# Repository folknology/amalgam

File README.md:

# Amalgam
Amalgam an OpenSource hardware fusion of FPGA and Cortex M7 Microcontroller in a [BlackEdge](https://github.com/folknology/BlackEdge) compatible layout, a project of the myStorm communtiy.

Current status is hardware design, you can see the developments we are making on my regular streams :
*  [Live Stream, 8pm BST](https://www.twitch.tv/folknology)
* [Historic streams](https://www.youtube.com/watch?v=79OoLG_Dxk0&list=PLXS9jyX9czzodpJNL-szsMfl0rOrZk4B7)
Or at the join us at the [myStorm community forum](https://forum.mystorm.uk)

We will be using an Alloy fusion framework on top of [nMigen](https://github.com/m-labs/nmigen) and [Circuit Python](https://github.com/adafruit/circuitpython) alonmg with verilog using [Yosys](https://github.com/YosysHQ/yosys)

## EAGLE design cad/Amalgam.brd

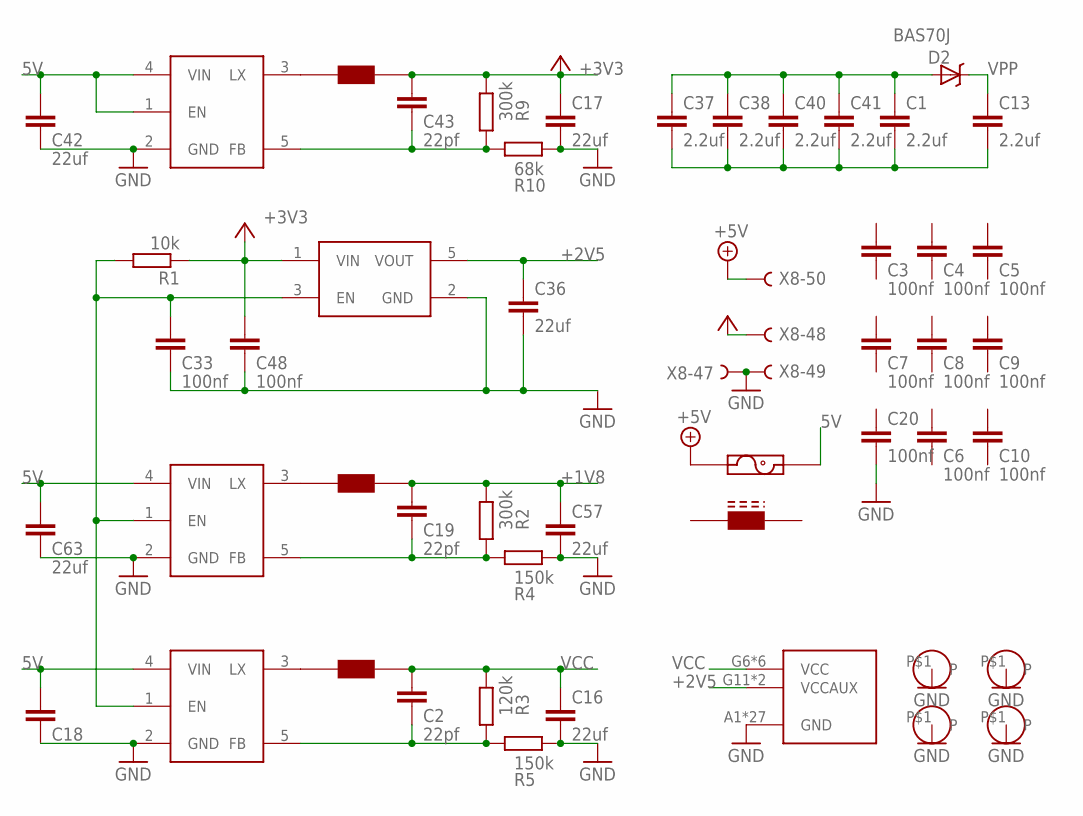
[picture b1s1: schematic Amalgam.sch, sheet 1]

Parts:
C1, C13, C37, C38, C40, C41: 2.2uf; C0603
C2, C19, C43: 22pf; C0402
C3, C4, C5, C6, C7, C8, C9, C10, C20, C33, C48: 100nf; C0402
C16, C17, C36, C57: 22uf; C0603
C18, C42, C63: 22uf; C0402
D2: BAS70J; SOD-323
IC7: NCP114; TSOP-5/SOT23-5
R1: 10k; R0402
R2, R9: 300k; R0402
R3: 120k; R0402
R4, R5: 150k; R0402
R10: 68k; R0402
U$1: PTC-1206; 1206
U$7, U$15, U$16, U$17: HOLE-2.5MM; 2.5MM-HOLE
U$12, U$13, U$20: AP3429/A; TSOP-5/SOT23-5
U$14: LFE5-XX256CABGA256; CABGA256
U$18, U$19, U$23: NRS4018; NRC4018
U$21: FERRITE_BEAD1206; 1206
X8: 1296-T50; 1296-50

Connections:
5V: C18.2, C42.2, C63.2, U$1.2, U$12.4 (VIN), U$13.4 (VIN), U$20.1 (EN), U$20.4 (VIN); also elsewhere on the board
+1V8: C19.2, C57.1, R2.2, U$19.P$2; also elsewhere on the board
+2V5: C36.1, IC7.5 (VOUT), U$14.G11 (VCCAUX), U$14.L7 (VCCAUX)
+3V3: C17.1, C43.2, C48.2, IC7.1 (VIN), R1.1, R9.2, U$23.P$2, X8.48; also elsewhere on the board
+5V: U$1.1, X8.50; also elsewhere on the board
GND: C16.2, C17.2, C18.1, C20.2, C33.1, C36.2, C42.1, C48.1, C57.2, C63.1, IC7.2 (GND), R4.2, R5.2, R10.2, U$7.P$1, U$12.2 (GND), U$13.2 (GND), U$14.A1 (GND), U$14.A16 (GND), U$14.D2 (GND), U$14.D15 (GND), U$14.F8 (GND), U$14.F9 (GND), U$14.G8 (GND), U$14.G10 (GND), U$14.H1 (GND), U$14.H8 (GND), U$14.H9 (GND), U$14.H10 (GND), U$14.H16 (GND), U$14.J8 (GND), U$14.J9 (GND), U$14.J10 (GND), U$14.K6 (GND), U$14.K7 (GND), U$14.K8 (GND), U$14.K9 (GND), U$14.K10 (GND), U$14.N2 (GND), U$14.N15 (GND), U$14.T1 (GND), U$14.T5 (GND), U$14.T12 (GND), U$14.T16 (GND), U$15.P$1, U$16.P$1, U$17.P$1, U$20.2 (GND), X8.47, X8.49; also elsewhere on the board
unnamed: C33.2, IC7.3 (EN), R1.2, U$12.1 (EN), U$13.1 (EN)
unnamed: C19.1, R2.1, R4.1, U$12.5 (FB)
unnamed: U$13.3 (LX), U$18.P$1
unnamed: U$12.3 (LX), U$19.P$1
unnamed: C2.1, R3.1, R5.1, U$13.5 (FB)
unnamed: C43.1, R9.1, R10.1, U$20.5 (FB)
unnamed: U$20.3 (LX), U$23.P$1
unnamed: C1.2, C13.2, C37.2, C38.2, C40.2, C41.2
unnamed: C1.1, C37.1, C38.1, C40.1, C41.1, D2.A
VCC: C2.2, C16.1, R3.2, U$14.G6 (VCC), U$14.G7 (VCC), U$14.G9 (VCC), U$14.L8 (VCC), U$14.L9 (VCC), U$14.L10 (VCC), U$18.P$2
VPP: C13.1, D2.C

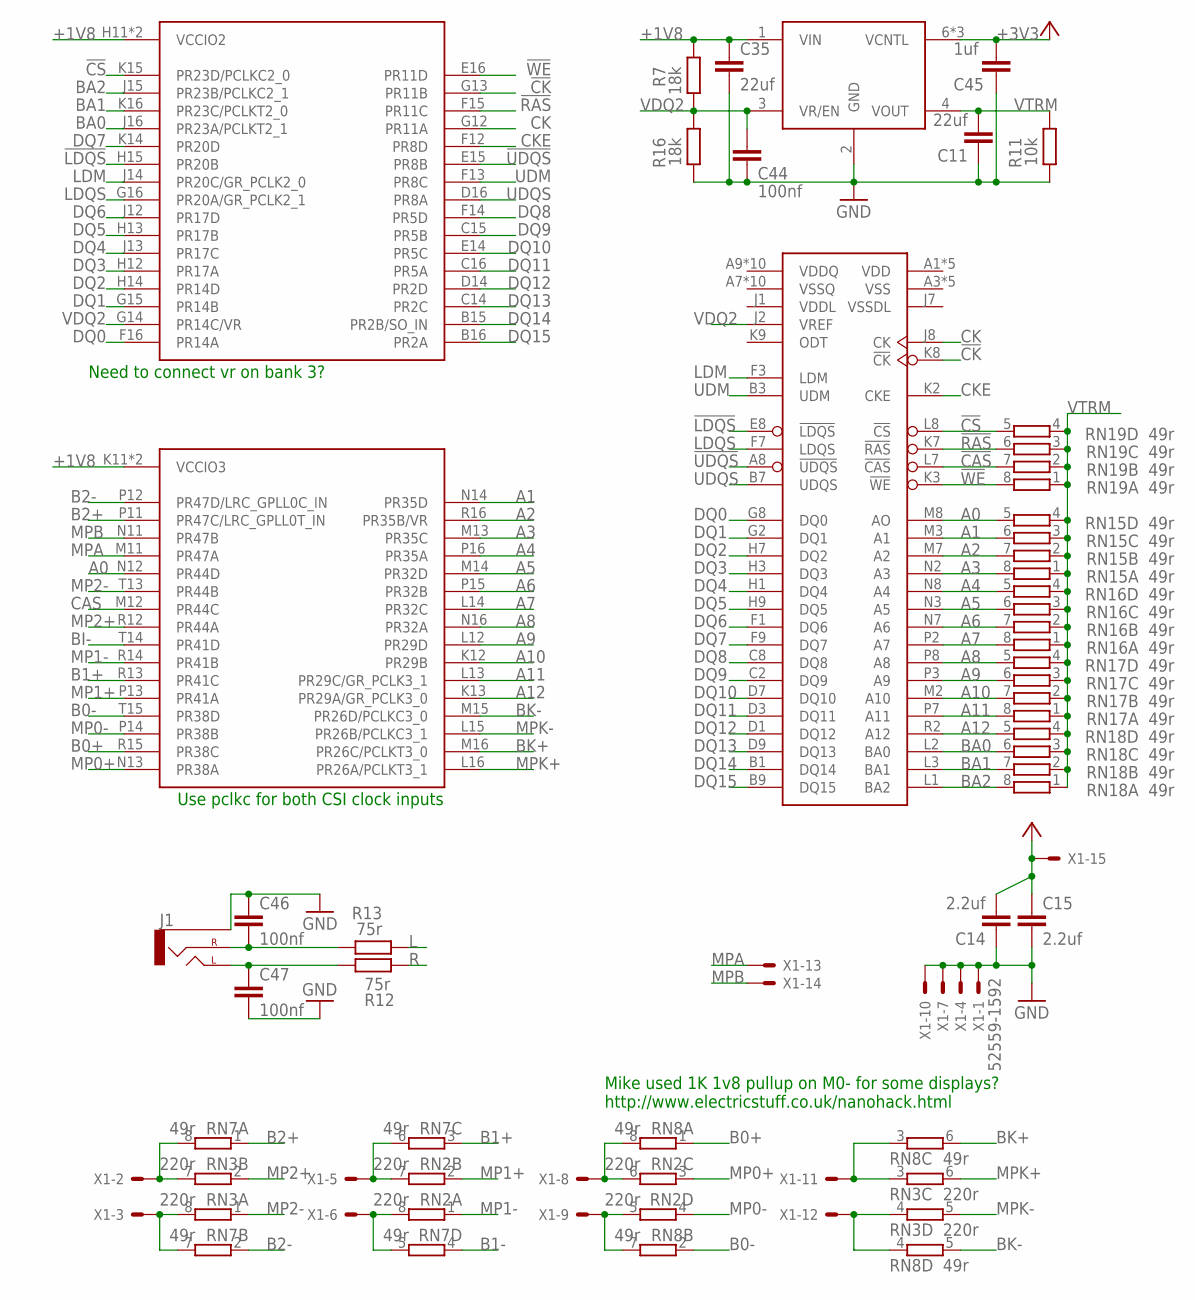
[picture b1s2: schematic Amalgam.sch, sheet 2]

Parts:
C11, C35: 22uf; C0603
C14, C15: 2.2uf; C0603
C44: 100nf; C0402
C45: 1uf; C0402
C46, C47: 100nf; C0603
J1: AUDIO_JACK_2.5MM_2.5MM_SMD; STEREOJACK2.5MM
R7, R16: 18k; R0402
R11: 10k; R0402
R12, R13: 75r; R0402
RN2, RN3: 220r; EXB38V
RN7, RN8, RN15, RN16, RN17, RN18, RN19: 49r; EXB38V
U$4: DDR2; WBGA-84
U$14: LFE5-XX256CABGA256; CABGA256
U$22: AP2303; SOIC-8-NARROW
X1: 52559-1592

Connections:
!CAS: RN19.7 (2), U$4.L7 (!CAS)
!CK: U$4.K8 (!CK), U$14.G13 (PR11B)
!CS: RN19.5 (2), U$4.L8 (!CS), U$14.K15 (PR23D/PCLKC2_0)
!LDQS: U$4.E8 (!LDQS), U$14.H15 (PR20B)
!RAS: RN19.6 (2), U$4.K7 (!RAS), U$14.F15 (PR11C)
!UDQS: U$4.A8 (!UDQS), U$14.E15 (PR8B)
!WE: RN19.8 (2), U$4.K3 (!WE), U$14.E16 (PR11D)
+1V8: C35.1, R7.1, U$14.H11 (VCCIO2), U$14.J11 (VCCIO2), U$14.K11 (VCCIO3), U$14.L11 (VCCIO3), U$22.1 (VIN); also elsewhere on the board
+3V3: C14.2, C15.1, C45.2, U$22.6 (VCNTL), U$22.7 (VCNTL), U$22.8 (VCNTL), X1.15; also elsewhere on the board
A0: RN15.5 (2), U$4.M8 (AO), U$14.N12 (PR44D)
A1: RN15.6 (2), U$4.M3 (A1), U$14.N14 (PR35D)
A2: RN15.7 (2), U$4.M7 (A2), U$14.R16 (PR35B/VR)
A3: RN15.8 (2), U$4.N2 (A3), U$14.M13 (PR35C)
A4: RN16.5 (2), U$4.N8 (A4), U$14.P16 (PR35A)
A5: RN16.6 (2), U$4.N3 (A5), U$14.M14 (PR32D)
A6: RN16.7 (2), U$4.N7 (A6), U$14.P15 (PR32B)
A7: RN16.8 (2), U$4.P2 (A7), U$14.L14 (PR32C)
A8: RN17.5 (2), U$4.P8 (A8), U$14.N16 (PR32A)
A9: RN17.6 (2), U$4.P3 (A9), U$14.L12 (PR29D)
A10: RN17.7 (2), U$4.M2 (A10), U$14.K12 (PR29B)
A11: RN17.8 (2), U$4.P7 (A11), U$14.L13 (PR29C/GR_PCLK3_1)
A12: RN18.5 (2), U$4.R2 (A12), U$14.K13 (PR29A/GR_PCLK3_0)
B0+: RN8.1, U$14.R15 (PR38C)
B0-: RN8.2 (1), U$14.T15 (PR38D)
B1+: RN7.3 (1), U$14.R13 (PR41C)
B1-: RN7.4 (1)
B2+: RN7.1, U$14.P11 (PR47C/LRC_GPLL0T_IN)
B2-: RN7.2 (1), U$14.P12 (PR47D/LRC_GPLL0C_IN)
BA0: RN18.6 (2), U$4.L2 (BA0), U$14.J16 (PR23A/PCLKT2_1)
BA1: RN18.7 (2), U$4.L3 (BA1), U$14.K16 (PR23C/PCLKT2_0)
BA2: RN18.8 (2), U$4.L1 (BA2), U$14.J15 (PR23B/PCLKC2_1)
BI-: U$14.T14 (PR41D)
BK+: RN8.6 (2), U$14.M16 (PR26C/PCLKT3_0)
BK-: RN8.5 (2), U$14.M15 (PR26D/PCLKC3_0)
CAS: U$14.M12 (PR44C)
CK: U$4.J8 (CK), U$14.G12 (PR11A)
CKE: U$4.K2 (CKE), U$14.F12 (PR8D)
DQ0: U$4.G8 (DQ0), U$14.F16 (PR14A)
DQ1: U$4.G2 (DQ1), U$14.G15 (PR14B)
DQ2: U$4.H7 (DQ2), U$14.H14 (PR14D)
DQ3: U$4.H3 (DQ3), U$14.H12 (PR17A)
DQ4: U$4.H1 (DQ4), U$14.J13 (PR17C)
DQ5: U$4.H9 (DQ5), U$14.H13 (PR17B)
DQ6: U$4.F1 (DQ6), U$14.J12 (PR17D)
DQ7: U$4.F9 (DQ7), U$14.K14 (PR20D)
DQ8: U$4.C8 (DQ8), U$14.F14 (PR5D)
DQ9: U$4.C2 (DQ9), U$14.C15 (PR5B)
DQ10: U$4.D7 (DQ10), U$14.E14 (PR5C)
DQ11: U$4.D3 (DQ11), U$14.C16 (PR5A)
DQ12: U$4.D1 (DQ12), U$14.D14 (PR2D)
DQ13: U$4.D9 (DQ13), U$14.C14 (PR2C)
DQ14: U$4.B1 (DQ14), U$14.B15 (PR2B/SO_IN)
DQ15: U$4.B9 (DQ15), U$14.B16 (PR2A)
GND: C11.1, C14.1, C15.2, C35.2, C44.1, C45.1, C46.1, C47.2, J1.5 (SLEEVE), R11.2, R16.2, U$22.2 (GND), X1.1, X1.4, X1.7, X1.10; also elsewhere on the board
L: R13.1; also elsewhere on the board
LDM: U$4.F3 (LDM), U$14.J14 (PR20C/GR_PCLK2_0)
LDQS: U$4.F7 (LDQS), U$14.G16 (PR20A/GR_PCLK2_1)
MP0+: RN2.3 (1), U$14.N13 (PR38A)
MP0-: RN2.4 (1), U$14.P14 (PR38B)
MP1+: RN2.2 (1), U$14.P13 (PR41A)
MP1-: RN2.1, U$14.R14 (PR41B)
MP2+: RN3.2 (1), U$14.R12 (PR44A)
MP2-: RN3.1, U$14.T13 (PR44B)
MPA: U$14.M11 (PR47A), X1.13
MPB: U$14.N11 (PR47B), X1.14
MPK+: RN3.6 (2), U$14.L16 (PR26A/PCLKT3_1)
MPK-: RN3.5 (2), U$14.L15 (PR26B/PCLKC3_1)
unnamed: RN3.3 (1), RN8.3 (1), X1.11
unnamed: RN3.4 (1), RN8.4 (1), X1.12
unnamed: RN2.6 (2), RN8.8 (2), X1.8
unnamed: RN2.5 (2), RN8.7 (2), X1.9
unnamed: RN2.7 (2), RN7.6 (2), X1.5
unnamed: RN2.8 (2), RN7.5 (2), X1.6
unnamed: RN3.8 (2), RN7.7 (2), X1.3
unnamed: RN3.7 (2), RN7.8 (2), X1.2
unnamed: C46.2, J1.4 (RIGHT), R13.2
unnamed: C47.1, J1.1 (LEFT), R12.1
R: R12.2; also elsewhere on the board
UDM: U$4.B3 (UDM), U$14.F13 (PR8C)
UDQS: U$4.B7 (UDQS), U$14.D16 (PR8A)
VDQ2: C44.2, R7.2, R16.1, U$4.J2 (VREF), U$14.G14 (PR14C/VR), U$22.3 (VR/EN)
VTRM: C11.2, R11.1, RN15.1, RN15.2 (1), RN15.3 (1), RN15.4 (1), RN16.1, RN16.2 (1), RN16.3 (1), RN16.4 (1), RN17.1, RN17.2 (1), RN17.3 (1), RN17.4 (1), RN18.1, RN18.2 (1), RN18.3 (1), RN18.4 (1), RN19.1, RN19.2 (1), RN19.3 (1), RN19.4 (1), U$22.4 (VOUT)

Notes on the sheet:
Need to connect vr on bank 3?
Use pclkc for both CSI clock inputs
Mike used 1K 1v8 pullup on M0- for some displays? http://www.electricstuff.co.uk/nanohack.html

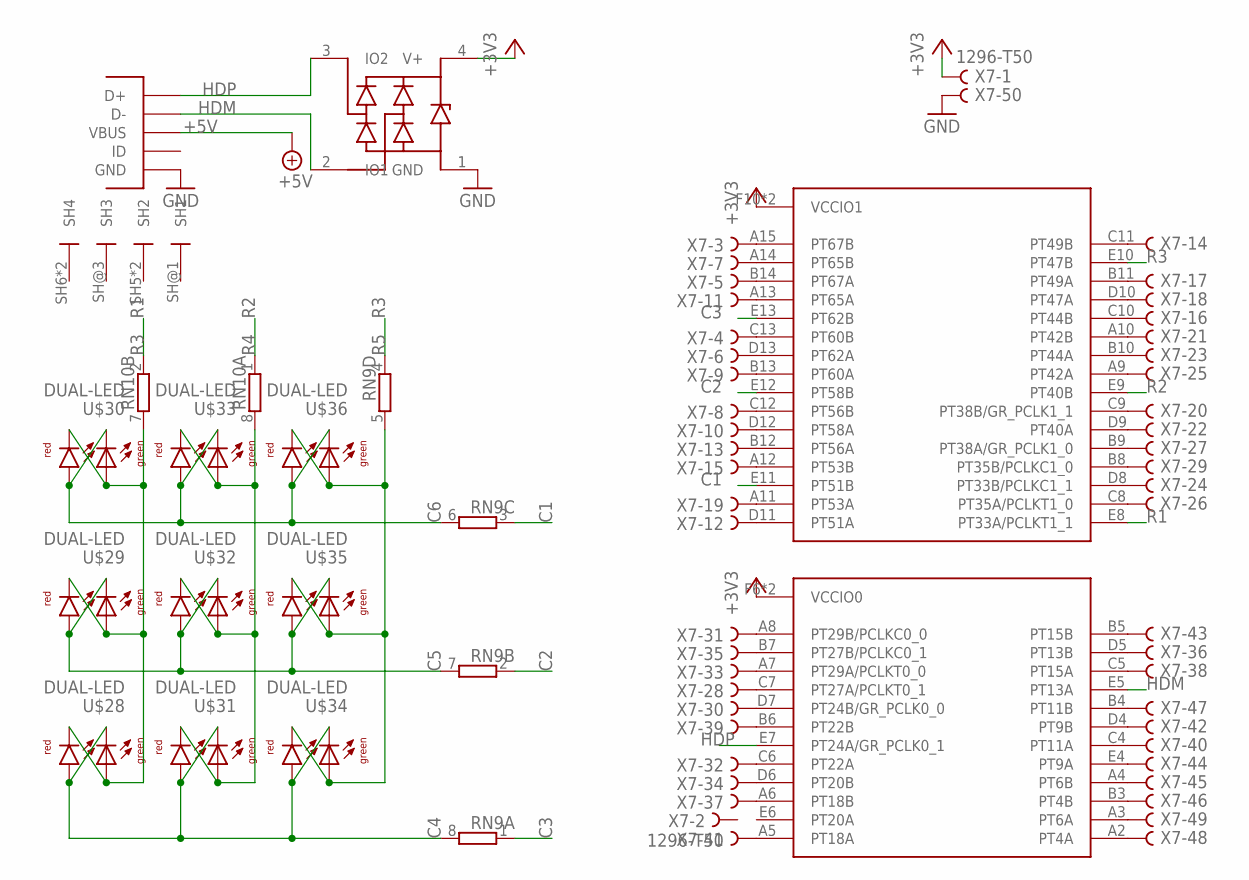
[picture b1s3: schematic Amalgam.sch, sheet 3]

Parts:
ESD1: PRTR5V0U2X; SOT143B
RN9, RN10: 4R-NEXB38V; EXB38V
U$11: FCI-MICROUSB-B-PEG; MICROUSB-B-PEG
U$14: LFE5-XX256CABGA256; CABGA256
U$28, U$29, U$30, U$31, U$32, U$33, U$34, U$35, U$36: DUAL-LED; DUAL-0603
X7: 1296-T50; 1296-50

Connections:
+3V3: ESD1.4 (V+), U$14.F6 (VCCIO0), U$14.F7 (VCCIO0), U$14.F10 (VCCIO1), U$14.F11 (VCCIO1), X7.1; also elsewhere on the board
+5V: U$11.P$1 (VBUS); also elsewhere on the board
C1: RN9.3 (1), U$14.E11 (PT51B)
C2: RN9.2 (1), U$14.E12 (PT58B)
C3: RN9.1, U$14.E13 (PT62B)
C4: RN9.8 (2), U$28.A1 (AR), U$28.C2 (CG), U$31.A1 (AR), U$31.C2 (CG), U$34.A1 (AR), U$34.C2 (CG)
C5: RN9.7 (2), U$29.A1 (AR), U$29.C2 (CG), U$32.A1 (AR), U$32.C2 (CG), U$35.A1 (AR), U$35.C2 (CG)
C6: RN9.6 (2), U$30.A1 (AR), U$30.C2 (CG), U$33.A1 (AR), U$33.C2 (CG), U$36.A1 (AR), U$36.C2 (CG)
GND: ESD1.1 (GND), U$11.P$5 (GND), X7.50; also elsewhere on the board
HDM: ESD1.2 (IO1), U$11.P$2 (D-), U$14.E5 (PT13A)
HDP: ESD1.3 (IO2), U$11.P$3 (D+), U$14.E7 (PT24A/GR_PCLK0_1)
unnamed: U$14.B3 (PT4B), X7.46
unnamed: U$14.A2 (PT4A), X7.48
unnamed: U$14.A15 (PT67B), X7.3
unnamed: U$14.B14 (PT67A), X7.5
unnamed: U$14.A14 (PT65B), X7.7
unnamed: U$14.B13 (PT60A), X7.9
unnamed: U$14.A13 (PT65A), X7.11
unnamed: U$14.B12 (PT56A), X7.13
unnamed: U$14.A12 (PT53B), X7.15
unnamed: U$14.B11 (PT49A), X7.17
unnamed: U$14.A11 (PT53A), X7.19
unnamed: U$14.C13 (PT60B), X7.4
unnamed: U$14.D13 (PT62A), X7.6
unnamed: U$14.C12 (PT56B), X7.8
unnamed: U$14.D12 (PT58A), X7.10
unnamed: U$14.A8 (PT29B/PCLKC0_0), X7.31
unnamed: U$14.A7 (PT29A/PCLKT0_0), X7.33
unnamed: U$14.B7 (PT27B/PCLKC0_1), X7.35
unnamed: U$14.A6 (PT18B), X7.37
unnamed: U$14.B6 (PT22B), X7.39
unnamed: U$14.A5 (PT18A), X7.41
unnamed: U$14.B5 (PT15B), X7.43
unnamed: U$14.C7 (PT27A/PCLKT0_1), X7.28
unnamed: U$14.D7 (PT24B/GR_PCLK0_0), X7.30
unnamed: U$14.C6 (PT22A), X7.32
unnamed: U$14.D6 (PT20B), X7.34
unnamed: U$14.D5 (PT13B), X7.36
unnamed: U$14.B4 (PT11B), X7.47
unnamed: U$14.A4 (PT6B), X7.45
unnamed: U$14.A3 (PT6A), X7.49
unnamed: U$14.D11 (PT51A), X7.12
unnamed: U$14.C11 (PT49B), X7.14
unnamed: U$14.C10 (PT44B), X7.16
unnamed: U$14.D10 (PT47A), X7.18
unnamed: U$14.A10 (PT42B), X7.21
unnamed: U$14.B10 (PT44A), X7.23
unnamed: U$14.A9 (PT42A), X7.25
unnamed: U$14.B9 (PT38A/GR_PCLK1_0), X7.27
unnamed: U$14.B8 (PT35B/PCLKC1_0), X7.29
unnamed: U$14.C9 (PT38B/GR_PCLK1_1), X7.20
unnamed: U$14.D9 (PT40A), X7.22
unnamed: U$14.D8 (PT33B/PCLKC1_1), X7.24
unnamed: U$14.C8 (PT35A/PCLKT1_0), X7.26
unnamed: U$14.C5 (PT15A), X7.38
unnamed: U$14.C4 (PT11A), X7.40
unnamed: U$14.D4 (PT9B), X7.42
unnamed: U$14.E4 (PT9A), X7.44
R1: RN10.2 (1), U$14.E8 (PT33A/PCLKT1_1)
R2: RN10.1, U$14.E9 (PT40B)
R3: RN9.4 (1), RN10.7 (2), U$14.E10 (PT47B), U$28.A2 (AG), U$28.C1 (CR), U$29.A2 (AG), U$29.C1 (CR), U$30.A2 (AG), U$30.C1 (CR)
R4: RN10.8 (2), U$31.A2 (AG), U$31.C1 (CR), U$32.A2 (AG), U$32.C1 (CR), U$33.A2 (AG), U$33.C1 (CR)
R5: RN9.5 (2), U$34.A2 (AG), U$34.C1 (CR), U$35.A2 (AG), U$35.C1 (CR), U$36.A2 (AG), U$36.C1 (CR)

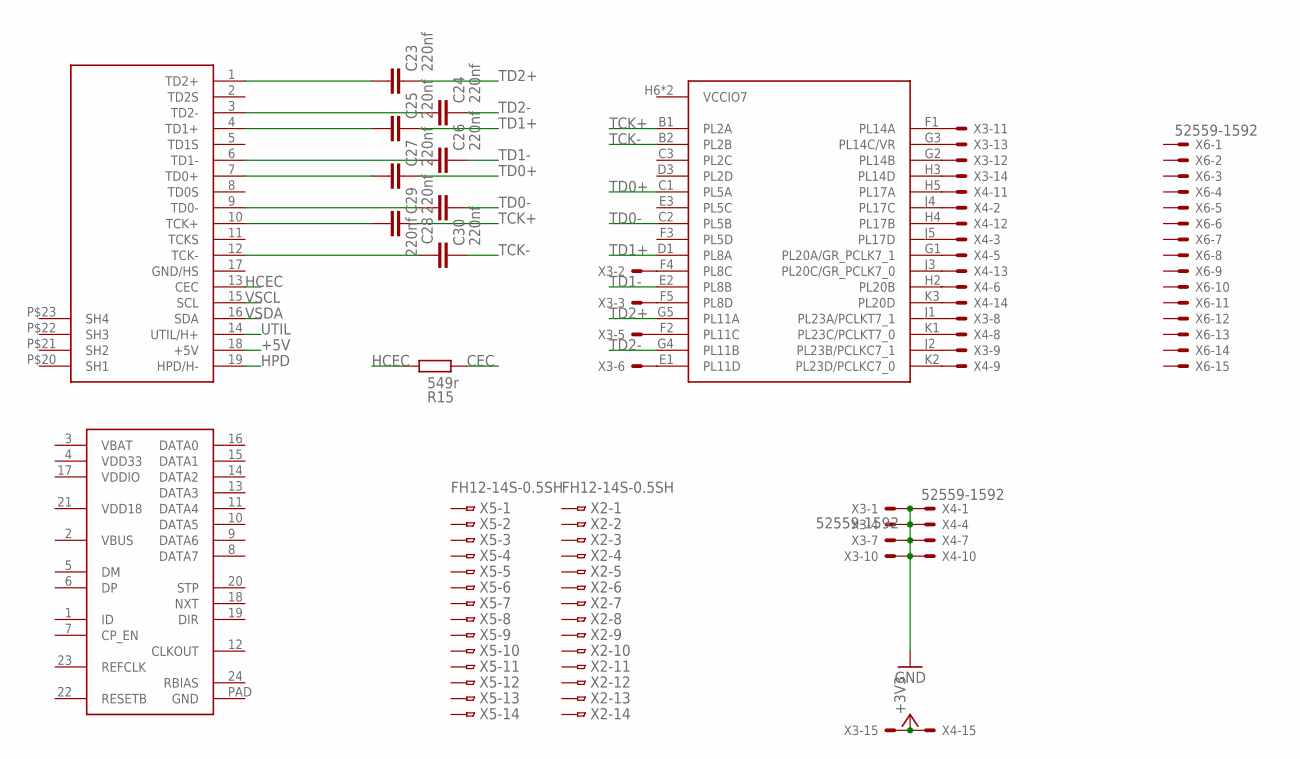
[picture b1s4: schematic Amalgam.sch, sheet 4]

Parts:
C23, C24, C25, C26, C27, C28, C29, C30: 220nf; C0402
R15: 549r; R0402
U$9: HD10-001_HDMIMINI-HDMI; MINI-HDMI
U$14: LFE5-XX256CABGA256; CABGA256
U$25: USB3318-QFN24; 24-QFN
X2, X5: FH12-14S-0.5SH
X3, X4, X6: 52559-1592

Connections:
+3V3: X3.15, X4.15; also elsewhere on the board
+5V: U$9.18 (+5V); also elsewhere on the board
CEC: R15.2; also elsewhere on the board
GND: U$25.PAD (GND), X3.1, X3.4, X3.7, X3.10, X4.1, X4.4, X4.7, X4.10; also elsewhere on the board
HCEC: R15.1, U$9.13 (CEC)
HPD: U$9.19 (HPD/H-); also elsewhere on the board
unnamed: U$14.K3 (PL20D), X4.14
unnamed: U$14.J3 (PL20C/GR_PCLK7_0), X4.13
unnamed: U$14.J1 (PL23A/PCLKT7_1), X3.8
unnamed: U$14.J2 (PL23B/PCLKC7_1), X3.9
unnamed: U$14.K1 (PL23C/PCLKT7_0), X4.8
unnamed: U$14.K2 (PL23D/PCLKC7_0), X4.9
unnamed: U$14.H2 (PL20B), X4.6
unnamed: U$14.G1 (PL20A/GR_PCLK7_1), X4.5
unnamed: U$14.J5 (PL17D), X4.3
unnamed: U$14.J4 (PL17C), X4.2
unnamed: U$14.H4 (PL17B), X4.12
unnamed: U$14.H5 (PL17A), X4.11
unnamed: U$14.H3 (PL14D), X3.14
unnamed: U$14.G3 (PL14C/VR), X3.13
unnamed: U$14.G2 (PL14B), X3.12
unnamed: U$14.F1 (PL14A), X3.11
unnamed: U$14.E1 (PL11D), X3.6
unnamed: U$14.F2 (PL11C), X3.5
unnamed: U$14.F5 (PL8D), X3.3
unnamed: C23.2, U$9.1 (TD2+)
unnamed: C24.2, U$9.3 (TD2-)
unnamed: C25.2, U$9.4 (TD1+)
unnamed: C26.2, U$9.6 (TD1-)
unnamed: C27.2, U$9.7 (TD0+)
unnamed: C28.1, U$9.9 (TD0-)
unnamed: C29.2, U$9.10 (TCK+)
unnamed: U$14.F4 (PL8C), X3.2
unnamed: C30.2, U$9.12 (TCK-)
TCK+: C29.1, U$14.B1 (PL2A)
TCK-: C30.1, U$14.B2 (PL2B)
TD0+: C27.1, U$14.C1 (PL5A)
TD0-: C28.2, U$14.C2 (PL5B)
TD1+: C25.1, U$14.D1 (PL8A)
TD1-: C26.1, U$14.E2 (PL8B)
TD2+: C23.1, U$14.G5 (PL11A)
TD2-: C24.1, U$14.G4 (PL11B)
UTIL: U$9.14 (UTIL/H+)
VBAT: U$25.3 (VBAT)
VDD18: U$25.21 (VDD18)
VDD33: U$25.4 (VDD33)
VDDIO: U$25.17 (VDDIO)
VSCL: U$9.15 (SCL); also elsewhere on the board
VSDA: U$9.16 (SDA); also elsewhere on the board

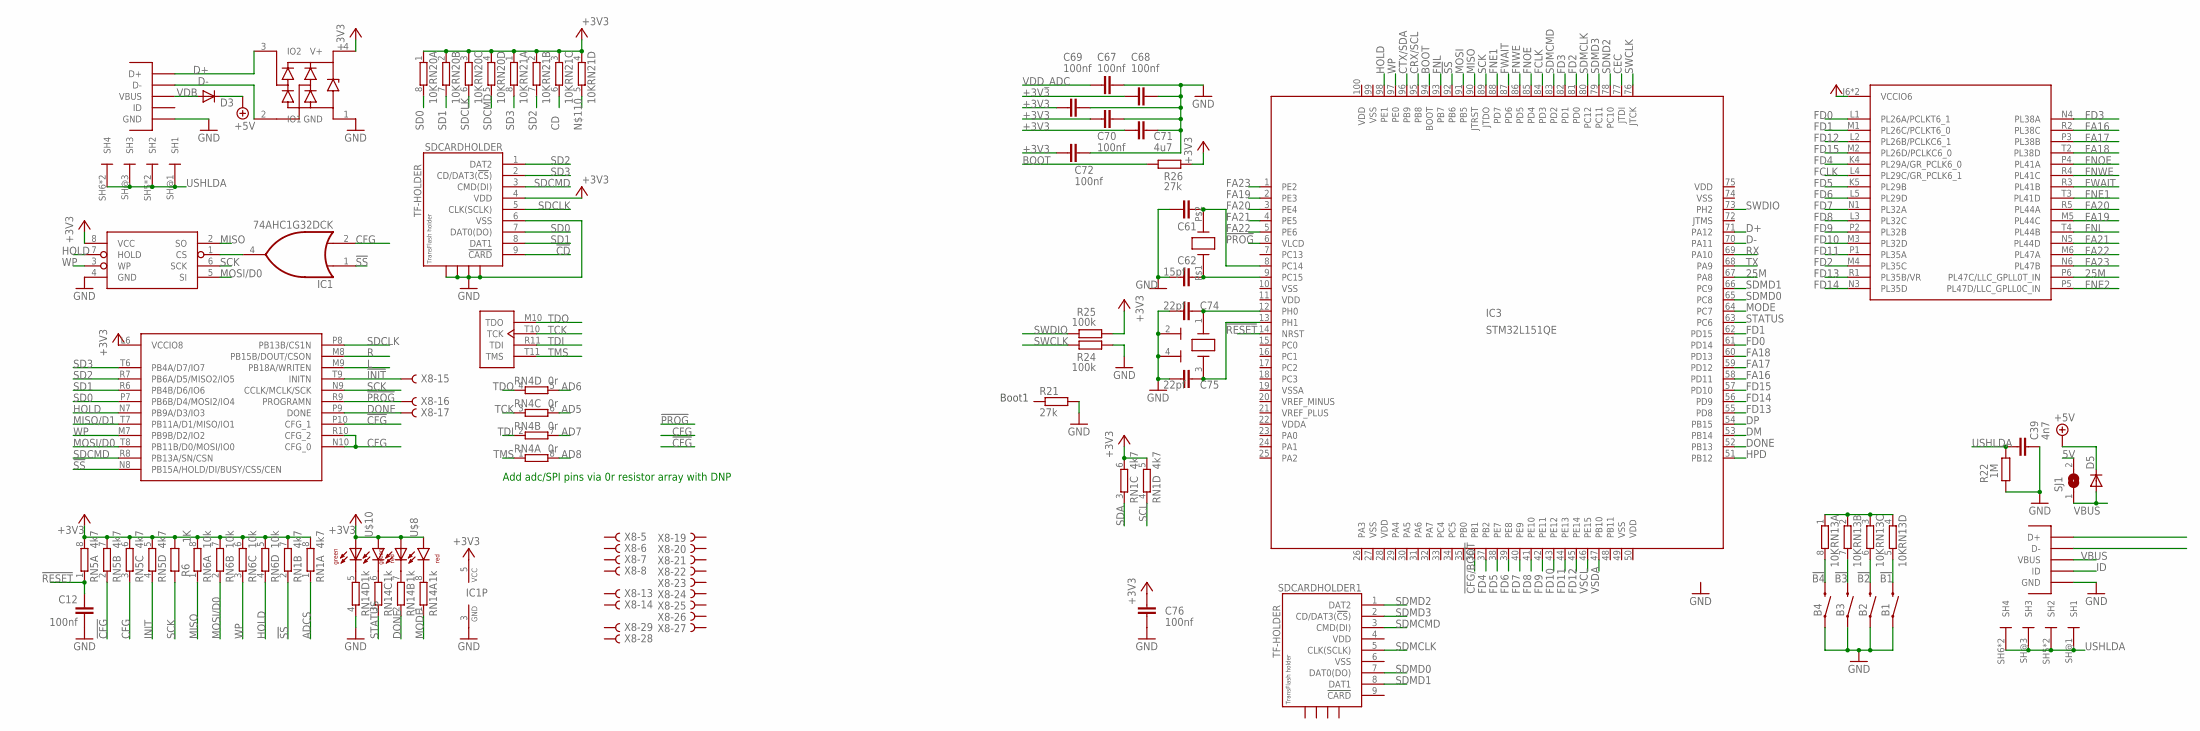
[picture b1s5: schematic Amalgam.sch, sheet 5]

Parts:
B1, B2, B3, B4: RS SWITCH; TACTILE-SWITCH-1101NE
C12, C67, C68, C69, C70, C72, C76: 100nf; C0402
C39: 4n7; C0402
C61, C62: 15pf; C0402
C71: 4u7; C0402
C74, C75: 22pf; C0402
D3, D5: DIODE-SOD123; SOD123
ESD2: PRTR5V0U2X; SOT143B
IC1: 74AHC1G32DCK; SC70-5
IC3: STM32L151QE; LQFP100_14X14
R6: 1K; R0402
R21, R26: 27k; R0402
R22: 1M; R0402
R24, R25: 100k; R0402
RN1, RN5: 4k7; EXB38V
RN4: 0r; EXB38V
RN6: 10k; EXB38V
RN13, RN20, RN21: 10K; EXB38V
RN14: 1k; EXB38V
SDCARDHOLDER, SDCARDHOLDER1: TF-HOLDER; TF-PULL
SJ1: SJ
U$2: AT25SDF041A; SOIC-8-NARROW
U$3: FC-135; FC135
U$5, U$6: FCI-MICROUSB-B-PEG; MICROUSB-B-PEG
U$8, U$10: DUAL-LED; DUAL-0603
U$14: LFE5-XX256CABGA256; CABGA256
X8: 1296-T50; 1296-50
Y3: 12MZ; CRYSTAL-3.2X2.5

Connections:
5V: SJ1.2; also elsewhere on the board
25M: IC3.67 (PA8), U$14.P6 (PL47C/LLC_GPLL0T_IN)
!B1: B1.2, RN13.5 (2)
!B2: B2.2, RN13.6 (2)
!B3: B3.2, RN13.7 (2)
!B4: B4.2, RN13.8 (2)
!CD: SDCARDHOLDER.9 (!CARD)
!CFG: RN5.2 (1), U$14.P10 (CFG_1)
!CFG/BOOT: IC3.36 (PB1)
!INIT: U$14.T9 (INITN), X8.15
!PROG: IC3.6 (VLCD), U$14.R9 (PROGRAMN), X8.16
!RESET: C12.1, IC3.14 (NRST), RN5.1
!SS: IC1.1 (I0), IC3.92 (PB6), RN1.2 (1), U$14.N8 (PB15A/HOLD/DI/BUSY/CSS/CEN)
+3V3: C68.2, C69.2, C70.2, C71.2, C72.2, C76.1, ESD2.4 (V+), IC1.5 (VCC), R6.2, R25.1, R26.2, RN1.5 (2), RN1.6 (2), RN1.7 (2), RN1.8 (2), RN5.5 (2), RN5.6 (2), RN5.7 (2), RN5.8 (2), RN6.5 (2), RN6.6 (2), RN6.7 (2), RN6.8 (2), RN20.1, RN20.2 (1), RN20.3 (1), RN20.4 (1), RN21.1, RN21.2 (1), RN21.3 (1), RN21.4 (1), SDCARDHOLDER.4 (VDD), U$2.8 (VCC), U$8.A1 (AR), U$8.A2 (AG), U$10.A1 (AR), U$10.A2 (AG), U$14.J6 (VCCIO6), U$14.J7 (VCCIO6), U$14.L6 (VCCIO8); also elsewhere on the board
+5V: D3.C, D5.C; also elsewhere on the board
AD5: RN4.6 (2)
AD6: RN4.5 (2)
AD7: RN4.7 (2)
AD8: RN4.8 (2)
ADCS: RN1.1
BOOT: IC3.94 (BOOT), R26.1
CD: RN21.6 (2)
CEC: IC3.77 (JTDI); also elsewhere on the board
CFG: IC1.2 (I1), RN5.3 (1), U$14.N10 (CFG_0), U$14.R10 (CFG_2)
CRX/SCL: IC3.95 (PB8)
CTX/SDA: IC3.96 (PB9)
D+: ESD2.3 (IO2), IC3.71 (PA12), U$5.P$3 (D+)
D-: ESD2.2 (IO1), IC3.70 (PA11), U$5.P$2 (D-)
DM: IC3.53 (PB14)
DONE: IC3.52 (PB13), RN14.2 (1), U$14.P9 (DONE), X8.17
DP: IC3.54 (PB15)
FA16: IC3.58 (PD11), U$14.R2 (PL38C)
FA17: IC3.59 (PD12), U$14.P3 (PL38B)
FA18: IC3.60 (PD13), U$14.T2 (PL38D)
FA19: IC3.2 (PE3), U$14.M5 (PL44C)
FA20: IC3.3 (PE4), U$14.R5 (PL44A)
FA21: IC3.4 (PE5), U$14.N5 (PL44D)
FA22: IC3.5 (PE6), U$14.M6 (PL47A)
FA23: IC3.1 (PE2), U$14.N6 (PL47B)
FCLK: IC3.84 (PD3), U$14.L4 (PL29C/GR_PCLK6_1)
FD0: IC3.61 (PD14), U$14.L1 (PL26A/PCLKT6_1)
FD1: IC3.62 (PD15), U$14.M1 (PL26C/PCLKT6_0)
FD2: IC3.81 (PD0), U$14.M4 (PL35C)
FD3: IC3.82 (PD1), U$14.N4 (PL38A)
FD4: IC3.37 (PB2), U$14.K4 (PL29A/GR_PCLK6_0)
FD5: IC3.38 (PE7), U$14.K5 (PL29B)
FD6: IC3.39 (PE8), U$14.L5 (PL29D)
FD7: IC3.40 (PE9), U$14.N1 (PL32A)
FD8: IC3.41 (PE10), U$14.L3 (PL32C)
FD9: IC3.42 (PE11), U$14.P2 (PL32B)
FD10: IC3.43 (PE12), U$14.M3 (PL32D)
FD11: IC3.44 (PE13), U$14.P1 (PL35A)
FD12: IC3.45 (PE14), U$14.L2 (PL26B/PCLKC6_1)
FD13: IC3.55 (PD8), U$14.R1 (PL35B/VR)
FD14: IC3.56 (PD9), U$14.N3 (PL35D)
FD15: IC3.57 (PD10), U$14.M2 (PL26D/PCLKC6_0)
FNE1: IC3.88 (PD7), U$14.T3 (PL41D)
FNE2: U$14.P5 (PL47D/LLC_GPLL0C_IN)
FNL: IC3.93 (PB7), U$14.T4 (PL44B)
FNOE: IC3.85 (PD4), U$14.P4 (PL41A)
FNWE: IC3.86 (PD5), U$14.R4 (PL41C)
FWAIT: IC3.87 (PD6), U$14.R3 (PL41B)
GND: B1.1, B2.1, B3.1, B4.1, C12.2, C39.1, C61.1, C62.1, C67.1, C68.1, C69.1, C70.1, C71.1, C72.1, C74.1, C75.1, C76.2, ESD2.1 (GND), IC1.3 (GND), R21.2, R22.2, R24.1, RN14.4 (1), SDCARDHOLDER.6 (VSS), SDCARDHOLDER.S1, SDCARDHOLDER.S2, SDCARDHOLDER.S3, SDCARDHOLDER.S4, U$2.4 (GND), U$5.P$5 (GND), U$6.P$5 (GND), Y3.2 (GND), Y3.4 (GND); also elsewhere on the board
HOLD: IC3.98 (PE1), RN6.4 (1), U$2.7 (HOLD), U$14.N7 (PB9A/D3/IO3)
HPD: IC3.51 (PB12); also elsewhere on the board
ID: U$6.P$4 (ID)
INIT: RN5.4 (1)
L: U$14.M9 (PB18A/WRITEN); also elsewhere on the board
MISO: IC3.90 (JTRST), RN6.1, U$2.2 (SO)
MISO/D1: U$14.T7 (PB11A/D1/MISO/IO1)
MODE: IC3.64 (PC7), RN14.1
MOSI: IC3.91 (PB5)
MOSI/D0: RN6.2 (1), U$2.5 (SI), U$14.T8 (PB11B/D0/MOSI/IO0)
unnamed: C62.2, IC3.9 (PC15), U$3.P$1 (X1)
unnamed: IC1.4 (O), U$2.1 (CS)
unnamed: RN13.1, RN13.2 (1), RN13.3 (1), RN13.4 (1)
unnamed: C61.2, IC3.8 (PC14), U$3.P$2 (X2)
unnamed: RN14.5 (2), U$10.C2 (CG)
unnamed: RN14.6 (2), U$10.C1 (CR)
unnamed: RN14.7 (2), U$8.C2 (CG)
unnamed: RN14.8 (2), U$8.C1 (CR)
unnamed: C75.2, IC3.13 (PH1), Y3.3 (X2)
unnamed: C74.2, IC3.12 (PH0), Y3.1 (X1)
R: U$14.M8 (PB15B/DOUT/CSON); also elsewhere on the board
RX: IC3.69 (PA10)
SCK: IC3.89 (JTDO), R6.1, U$2.6 (SCK), U$14.N9 (CCLK/MCLK/SCK)
SCL: RN1.4 (1)
SD0: RN20.8 (2), SDCARDHOLDER.7 (DAT0(DO)), U$14.P7 (PB6B/D4/MOSI2/IO4)
SD1: RN20.7 (2), SDCARDHOLDER.8 (DAT1), U$14.R6 (PB4B/D6/IO6)
SD2: RN21.7 (2), SDCARDHOLDER.1 (DAT2), U$14.R7 (PB6A/D5/MISO2/IO5)
SD3: RN21.8 (2), SDCARDHOLDER.2 (CD/DAT3(!CS!)), U$14.T6 (PB4A/D7/IO7)
SDA: RN1.3 (1)
SDCLK: RN20.6 (2), SDCARDHOLDER.5 (CLK(SCLK)), U$14.P8 (PB13B/CS1N)
SDCMD: RN20.5 (2), SDCARDHOLDER.3 (CMD(DI)), U$14.R8 (PB13A/SN/CSN)
SDMCLK: IC3.80 (PC12), SDCARDHOLDER1.5 (CLK(SCLK))
SDMCMD: IC3.83 (PD2), SDCARDHOLDER1.3 (CMD(DI))
SDMD0: IC3.65 (PC8), SDCARDHOLDER1.7 (DAT0(DO))
SDMD1: IC3.66 (PC9), SDCARDHOLDER1.8 (DAT1)
SDMD2: SDCARDHOLDER1.1 (DAT2)
SDMD3: IC3.79 (PC11), SDCARDHOLDER1.2 (CD/DAT3(!CS!))
SDND2: IC3.78 (PC10)
STATUS: IC3.63 (PC6), RN14.3 (1)
SWCLK: IC3.76 (JTCK), R24.2
SWDIO: IC3.73 (PH2), R25.2
TCK: RN4.3 (1), U$14.T10 (TCK)
TDI: RN4.2 (1), U$14.R11 (TDI)
TDO: RN4.4 (1), U$14.M10 (TDO)
TMS: RN4.1, U$14.T11 (TMS)
TX: IC3.68 (PA9)
USHLDA: C39.2, R22.1, U$5.SH5 (SH2), U$5.SH6 (SH4), U$5.SH@1 (SH1), U$5.SH@2 (SH2), U$5.SH@3 (SH3), U$5.SH@4 (SH4), U$6.SH5 (SH2), U$6.SH6 (SH4), U$6.SH@1 (SH1), U$6.SH@2 (SH2), U$6.SH@3 (SH3), U$6.SH@4 (SH4)
VBUS: D5.A, SJ1.1, U$6.P$1 (VBUS)
VDB: D3.A, U$5.P$1 (VBUS)
VDD: IC3.11 (VDD), IC3.28 (VDD), IC3.50 (VDD), IC3.75 (VDD), IC3.100 (VDD), SDCARDHOLDER1.4 (VDD)
VDDA: IC3.22 (VDDA)
VDD_ADC: C67.2
VSCL: IC3.46 (PE15); also elsewhere on the board
VSDA: IC3.47 (PB10); also elsewhere on the board
VSS: IC3.10 (VSS), IC3.27 (VSS), IC3.49 (VSS), IC3.74 (VSS), IC3.99 (VSS), SDCARDHOLDER1.6 (VSS)
VSSA: IC3.19 (VSSA)
WP: IC3.97 (PE0), RN6.3 (1), U$2.3 (WP), U$14.M7 (PB9B/D2/IO2)

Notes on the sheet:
Add adc/SPI pins via 0r resistor array with DNP
Boot1

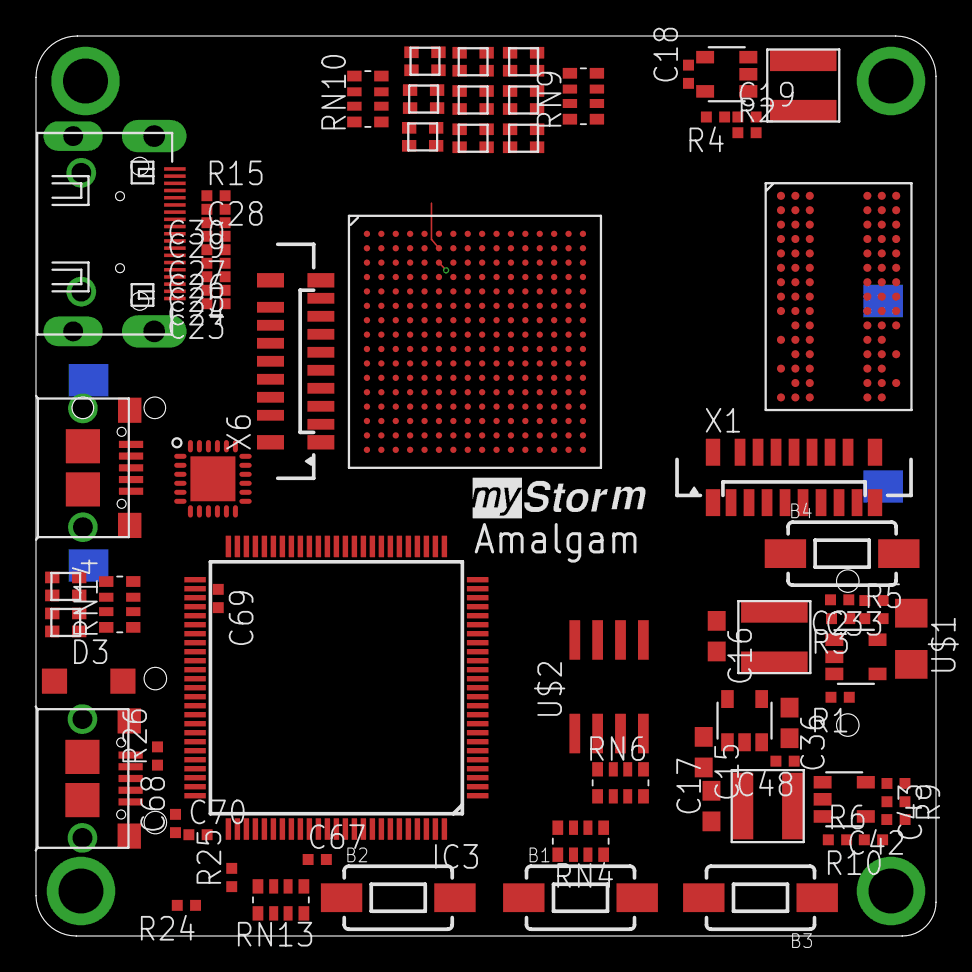
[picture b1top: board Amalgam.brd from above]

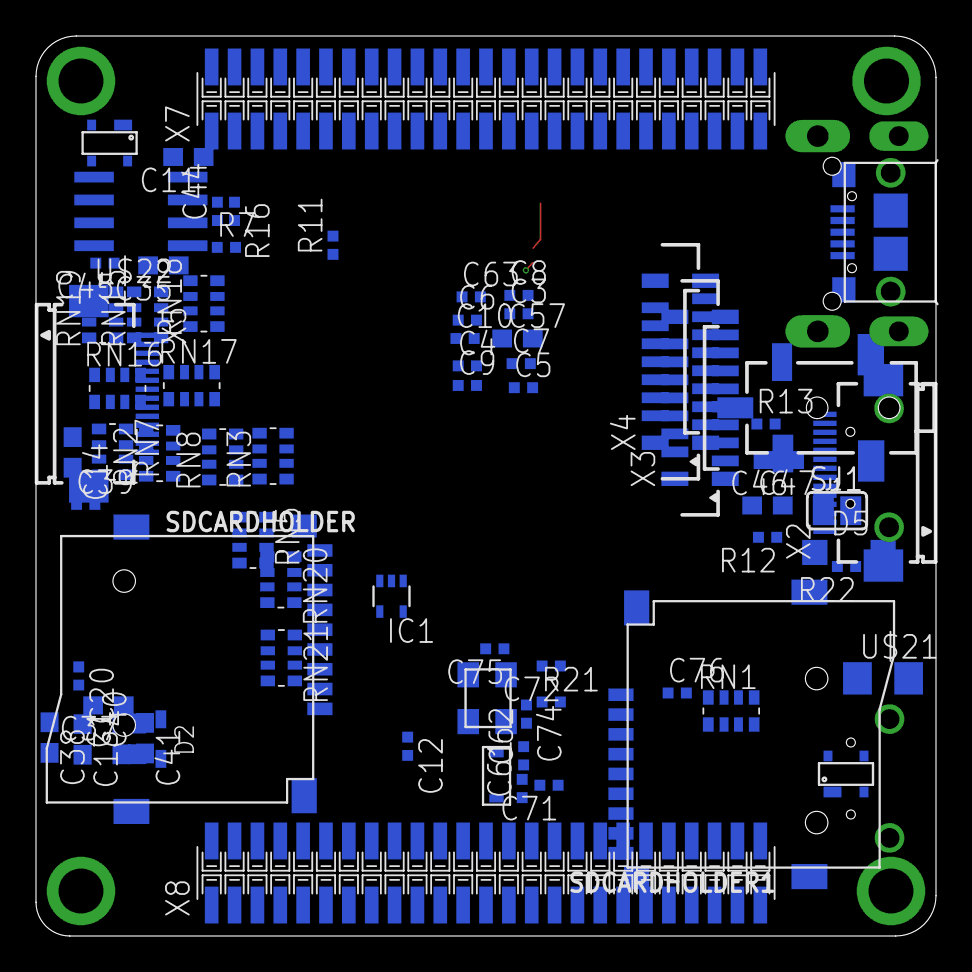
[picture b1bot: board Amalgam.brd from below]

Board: 4 copper layers, 50.0 x 50.0 mm, 152 parts (73 on the bottom side), 278 nets.

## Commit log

2020-09-19 Amalgam initial reorganisation from E5 repository into new project name
2020-09-19 Corrected Image layout file and links in readme
2020-09-20 Fixed typos added ref to Yosys

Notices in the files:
parts and their libraries:
SparkFun-Electromechanical: Licensing: Creative Commons ShareAlike 4.0 International - https://creativecommons.org/licenses/by-sa/4.0
